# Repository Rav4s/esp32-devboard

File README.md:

# esp32-devboard
Development board for the ESP32 :P

TODO: all other notes...

## BOM
IBOM: BOM/ibom.html (download and view in browser)  
Mouser Cart: https://www.mouser.com/ProjectManager/ProjectDetail.aspx?AccessID=de87a8ab7b

## Ideas
key ring size, button, leds, how to pwr??, thread/matter for smth? cool enclosure..., NFC, ENIG
board should be dragon shaped heheh or smth else scary LED EYES ORANGE

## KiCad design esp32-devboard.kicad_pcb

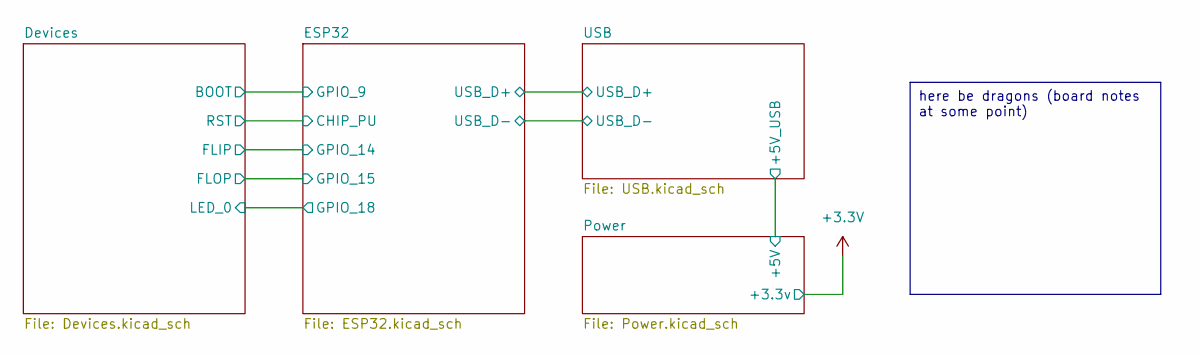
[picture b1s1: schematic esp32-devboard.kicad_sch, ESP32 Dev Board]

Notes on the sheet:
here be dragons (board notes at some point)

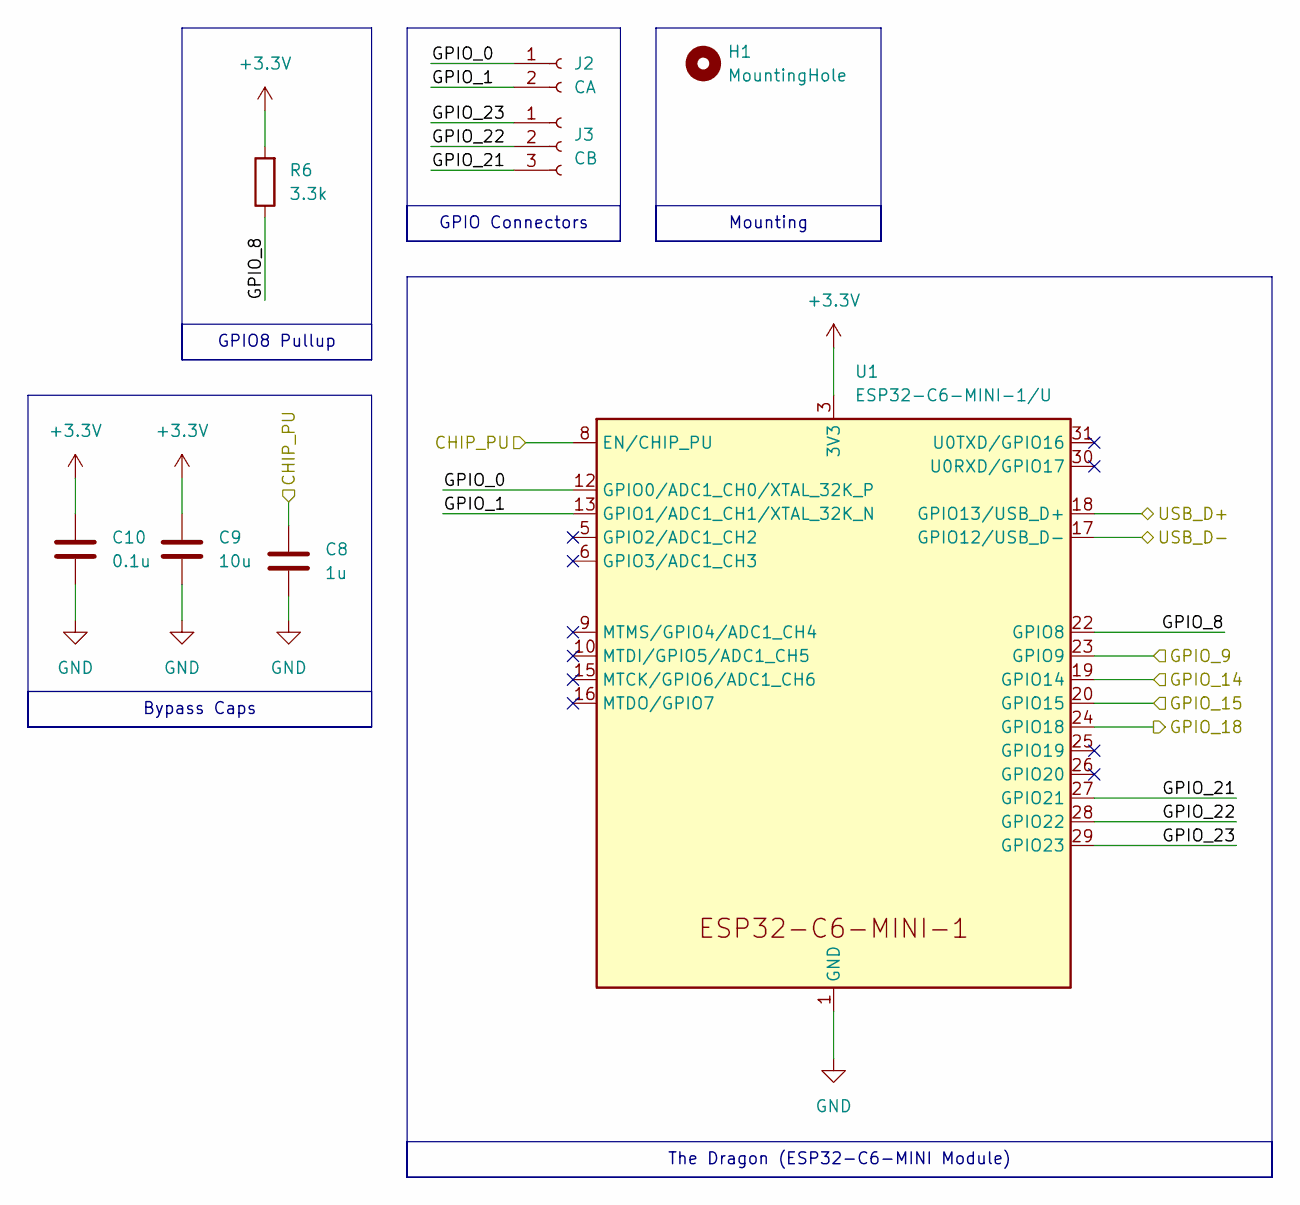
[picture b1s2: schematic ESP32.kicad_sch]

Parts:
C8: 1u; C_0603_1608Metric
C9: 10u; C_0603_1608Metric
C10: 0.1u; C_0603_1608Metric
H1: MountingHole; MountingHole_2.2mm_M2
J2: CA; PinHeader_1x02_P2.54mm_Vertical
J3: CB; PinHeader_1x03_P2.54mm_Vertical
R6: 3.3k; R_0603_1608Metric
U1: ESP32-C6-MINI-1/U; ESP32-C6-MINI-1

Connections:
+3.3V: C9.1, C10.1, R6.2, U1.3 (3V3); also elsewhere on the board
/Devices/BOOT: U1.23 (GPIO9); also elsewhere on the board
/Devices/FLIP: U1.19 (GPIO14); also elsewhere on the board
/Devices/FLOP: U1.20 (GPIO15); also elsewhere on the board
/Devices/LED_0: U1.24 (GPIO18); also elsewhere on the board
/Devices/RST: C8.1, U1.8 (EN/CHIP_PU); also elsewhere on the board
/ESP32/GPIO_0: J2.1, U1.12 (GPIO0/ADC1_CH0/XTAL_32K_P)
/ESP32/GPIO_1: J2.2, U1.13 (GPIO1/ADC1_CH1/XTAL_32K_N)
/ESP32/GPIO_8: R6.1, U1.22 (GPIO8)
/ESP32/GPIO_21: J3.3, U1.27 (GPIO21)
/ESP32/GPIO_22: J3.2, U1.28 (GPIO22)
/ESP32/GPIO_23: J3.1, U1.29 (GPIO23)
/ESP32/USB_D+: U1.18 (GPIO13/USB_D+); also elsewhere on the board
/ESP32/USB_D-: U1.17 (GPIO12/USB_D-); also elsewhere on the board
GND: C8.2, C9.2, C10.2, U1.1 (GND), U1.2 (GND), U1.11 (GND), U1.14 (GND), U1.36 (GND), U1.37 (GND), U1.38 (GND), U1.39 (GND), U1.40 (GND), U1.41 (GND), U1.42 (GND), U1.43 (GND), U1.44 (GND), U1.45 (GND), U1.46 (GND), U1.47 (GND), U1.48 (GND), U1.49 (GND), U1.50 (GND), U1.51 (GND), U1.52 (GND), U1.53 (GND); also elsewhere on the board

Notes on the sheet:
GPIO8 Pullup
Bypass Caps
GPIO Connectors
The Dragon (ESP32-C6-MINI Module)
Mounting

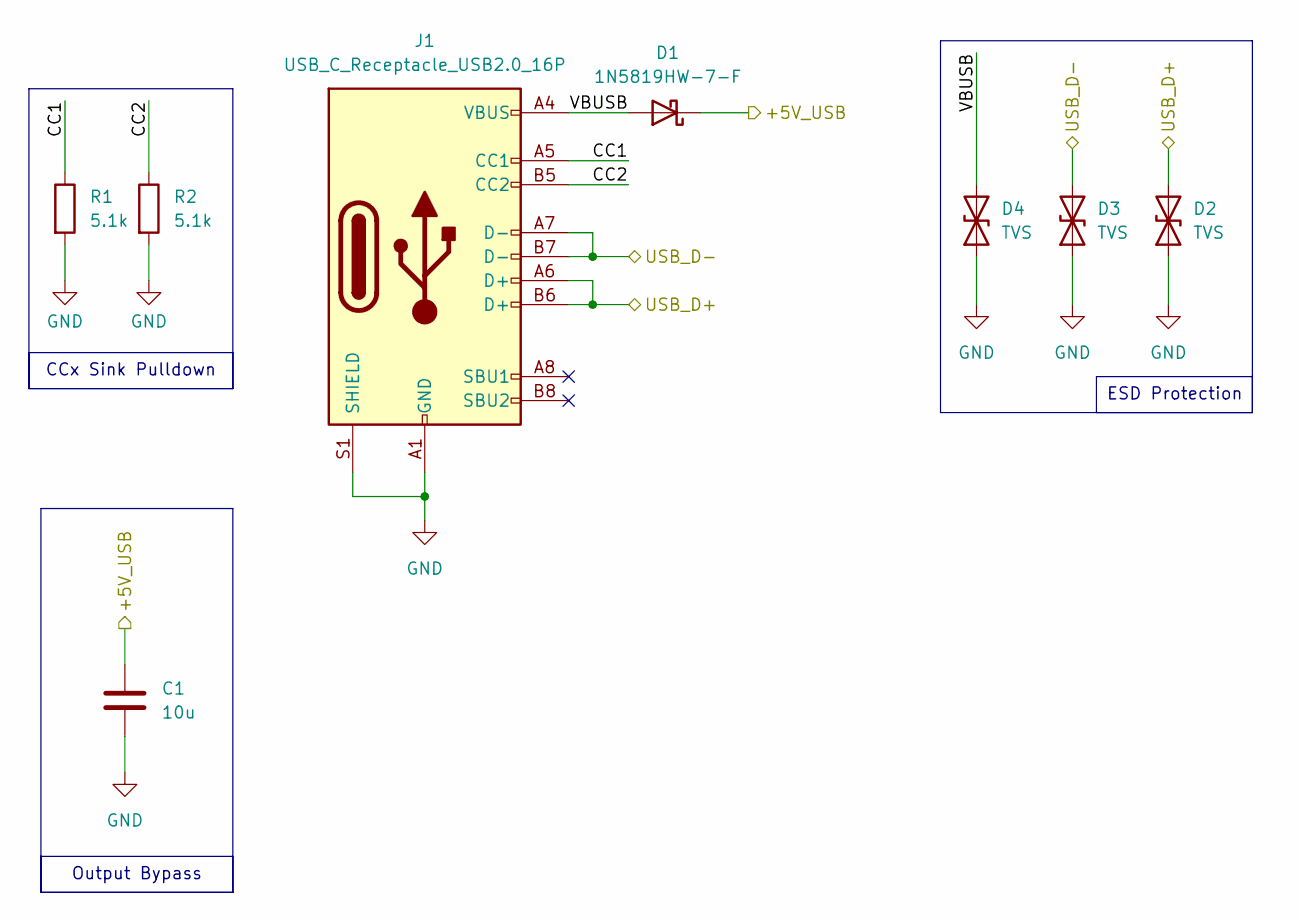
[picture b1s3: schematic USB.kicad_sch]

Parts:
C1: 10u; C_0603_1608Metric
D1: 1N5819HW-7-F; D_SOD-123
D2, D3, D4: TVS; D_0603_1608Metric
J1: USB_C_Receptacle_USB2.0_16P; USB_C_Receptacle_GCT_USB4105-xx-A_16P_TopMnt_Horizontal
R1, R2: 5.1k; R_0603_1608Metric

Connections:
/ESP32/USB_D+: D2.2 (A2), J1.A6 (D+), J1.B6 (D+); also elsewhere on the board
/ESP32/USB_D-: D3.2 (A2), J1.A7 (D-), J1.B7 (D-); also elsewhere on the board
/Power/+5V: C1.1, D1.1 (K); also elsewhere on the board
/USB/CC1: J1.A5 (CC1), R1.1
/USB/CC2: J1.B5 (CC2), R2.1
/USB/VBUSB: D1.2 (A), D4.2 (A2), J1.A4 (VBUS), J1.A9 (VBUS), J1.B4 (VBUS), J1.B9 (VBUS)
GND: C1.2, D2.1 (A1), D3.1 (A1), D4.1 (A1), J1.A1 (GND), J1.A12 (GND), J1.B1 (GND), J1.B12 (GND), J1.S1 (SHIELD), R1.2, R2.2; also elsewhere on the board

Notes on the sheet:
Output Bypass
ESD Protection
CCx Sink Pulldown

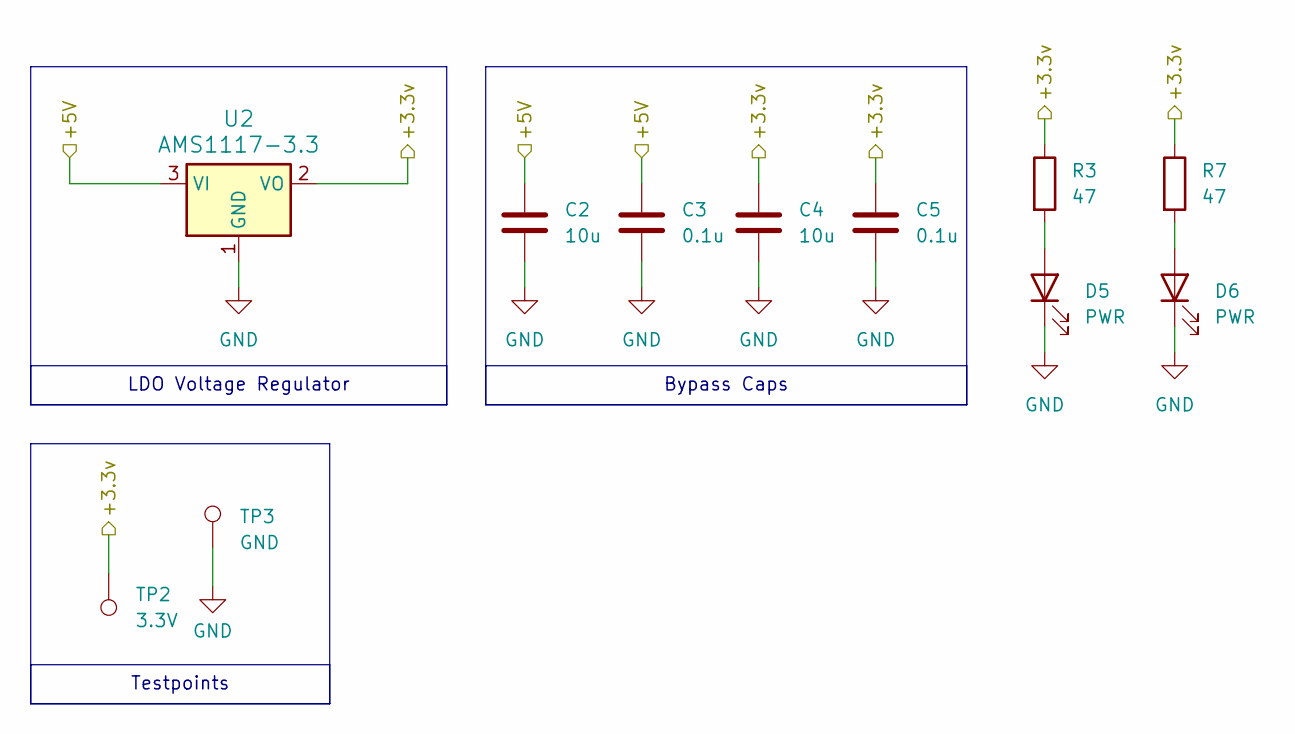
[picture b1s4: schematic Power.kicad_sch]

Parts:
C2, C4: 10u; C_0603_1608Metric
C3, C5: 0.1u; C_0603_1608Metric
D5, D6: PWR; LED_0603_1608Metric
R3, R7: 47; R_0603_1608Metric
TP2: 3.3V; TestPoint_Pad_D1.0mm
TP3: GND; TestPoint_Pad_D1.0mm
U2: AMS1117-3.3; SOT-223-3_TabPin2

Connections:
+3.3V: C4.1, C5.1, R3.1, R7.1, TP2.1, U2.2 (VO); also elsewhere on the board
/Power/+5V: C2.1, C3.1, U2.3 (VI); also elsewhere on the board
GND: C2.2, C3.2, C4.2, C5.2, D5.1 (K), D6.1 (K), TP3.1, U2.1 (GND); also elsewhere on the board
unnamed: D5.2 (A), R3.2
unnamed: D6.2 (A), R7.2

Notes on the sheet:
Testpoints
Bypass Caps
LDO Voltage Regulator

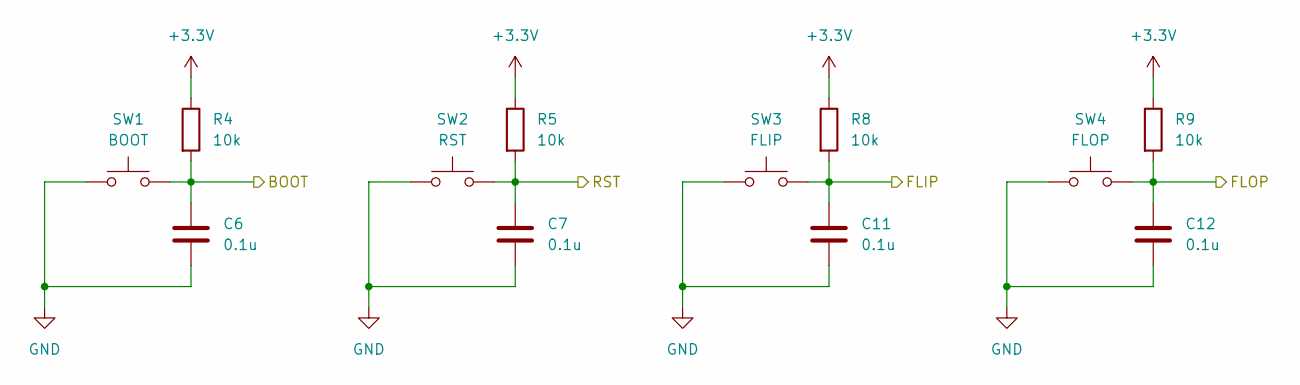
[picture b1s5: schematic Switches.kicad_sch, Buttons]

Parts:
C6, C7, C11, C12: 0.1u; C_0603_1608Metric
R4, R5, R8, R9: 10k; R_0603_1608Metric
SW1: BOOT; SW_Push_1P1T_NO_CK_KMR2
SW2: RST; SW_Push_1P1T_NO_CK_KMR2
SW3: FLIP; SW_Push_1P1T_NO_CK_KMR2
SW4: FLOP; SW_Push_1P1T_NO_CK_KMR2

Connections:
+3.3V: R4.1, R5.1, R8.1, R9.1; also elsewhere on the board
/Devices/BOOT: C6.1, R4.2, SW1.2; also elsewhere on the board
/Devices/FLIP: C11.1, R8.2, SW3.2; also elsewhere on the board
/Devices/FLOP: C12.1, R9.2, SW4.2; also elsewhere on the board
/Devices/RST: C7.1, R5.2, SW2.2; also elsewhere on the board
GND: C6.2, C7.2, C11.2, C12.2, SW1.1, SW2.1, SW3.1, SW4.1; also elsewhere on the board

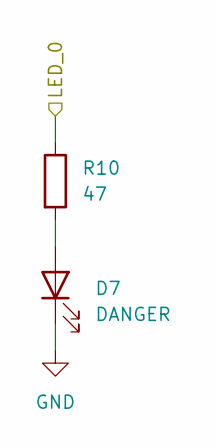
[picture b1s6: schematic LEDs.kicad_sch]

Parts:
D7: DANGER; LED_0603_1608Metric
R10: 47; R_0603_1608Metric

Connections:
/Devices/LED_0: R10.1; also elsewhere on the board
GND: D7.1 (K); also elsewhere on the board
unnamed: D7.2 (A), R10.2

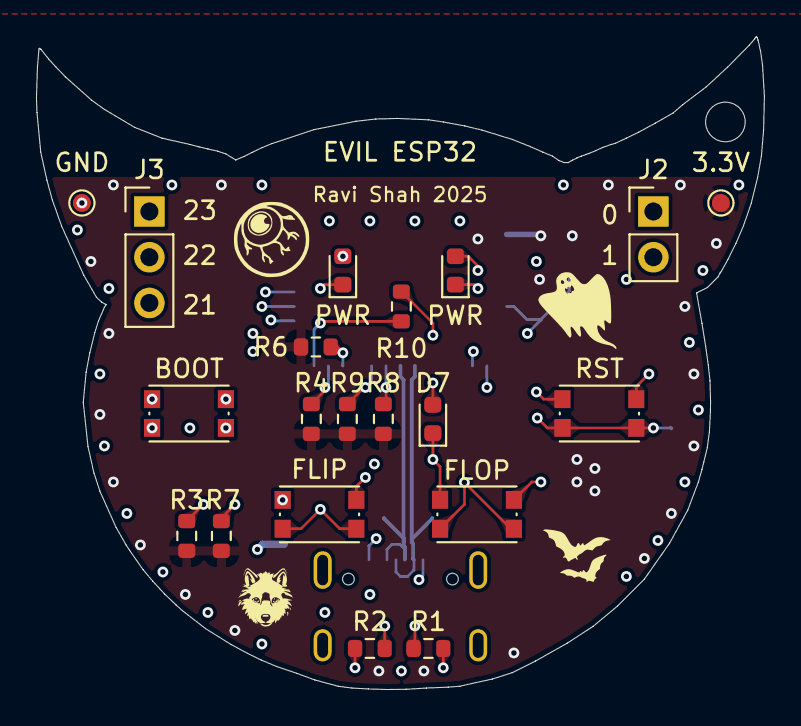
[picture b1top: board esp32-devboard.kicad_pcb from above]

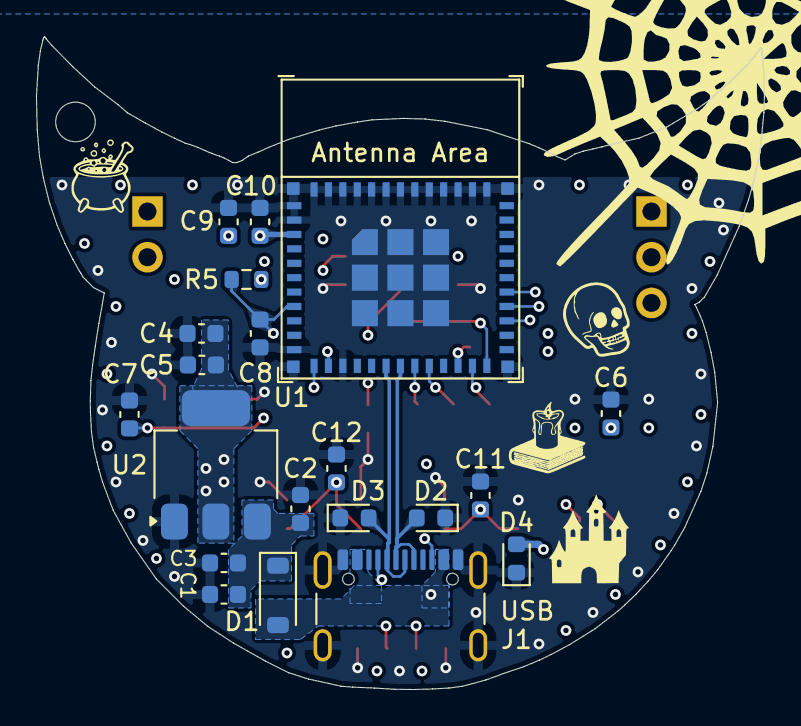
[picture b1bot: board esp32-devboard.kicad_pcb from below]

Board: 4 copper layers, 40.4 x 36.3 mm, 41 parts (20 on the bottom side), 22 nets.

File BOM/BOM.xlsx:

Reference | Value | Qty | P/N
C1,C2,C4,C9 | 10u | 4 | MLAST168BB5106MTNA01
C3,C5,C6,C7,C10,C11,C12 | 0.1u | 7 | UMK107B7104KAHT
C8 | 1u | 1 | C0603X105J4RAC7411
D1 | 1N5819HW-7-F | 1 | 1N5819HW-7-F
D2,D3,D4 | TVS | 3 | CPDUC5V0R-HF
D5,D6,D7 | -- mixed values -- | 3 | HSML-C191
J1 | USB_C_Receptacle_USB2.0_16P | 1 | 640-USB4215-03-A
J2 | CA | 1 | 54101-S0802LF
J3 | CB | 1 | 54101-S0803LF
R1,R2 | 5.1k | 2 | CRCW06035K10FKEC
R3,R7,R10 | 47 | 3 | MCT06030C4709FP500
R4,R5,R9 | 10k | 3 | MCT0603PD1002DP500
R6 | 3.3k | 1 | ERA-3APB332V
R8 | 10k | 1 | MCT0603PD1002DP500
SW1,SW2,SW3,SW4 | -- mixed values -- | 4 | KMR231GLFS
TP2,TP3 | -- mixed values -- | 2
U1 | ESP32-C6-MINI-1/U | 1 | ESP32-C6-MINI-1/U
U2 | AMS1117-3.3 | 1 | AMS1117-3.3

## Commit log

2025-02-02 add initial file structure
2025-02-02 added USB-C connector
2025-02-05 USB and PWR sch
2025-02-05 add BOOT/RST switches
2025-02-05 finished sch? (need P/Ns)
2025-02-05 add P/N
2025-02-06 assign footprints
2025-02-06 add testpoints
2025-02-06 LDO layout>
2025-02-06 more pwr stuff
2025-02-07 more layout & custom edge cuts
2025-02-07 zone fills & button layout
2025-02-07 more layout (dont look at this)
2025-02-07 almost done with layout
2025-02-07 layout kinda done
2025-02-07 USB routing
2025-02-07 initial routing
2025-02-08 stupid dumb drc
2025-02-08 todos
2025-02-09 add BOM
2025-02-09 IBOM
2025-02-09 readme, mounting holes, minor silk changes
2025-02-09 add cool silkscreen
2025-02-09 regenerate gerbers
2025-02-10 switch caps for lower cost
